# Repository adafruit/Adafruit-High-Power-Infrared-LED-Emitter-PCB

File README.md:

## Adafruit High Power Infrared LED Emitter PCB

<a href="http://www.adafruit.com/products/5639"><br/>
Click here to purchase one from the Adafruit shop</a>

PCB files for the Adafruit High Power Infrared LED Emitter. 

Format is EagleCAD schematic and board layout
* https://www.adafruit.com/product/5639

### Description

*pew* *pew*! This board is like a little ray gun for infrared light, with two high powered LED outputs. When controlled with the onboard N-Channel FET driver, you'll be blasting 100mA-200mA of current pulsing through each LED for 10+ meters of range! This is the easiest way to get great IR emitter range without wiring up a bunch of parts.

By using a 2mm pitch STEMMA JST PH cable with headers or alligator clips on the end, you can easily wire this board up without any soldering at all.

This board features a power transistor so you just need to provide about 3-5V DC power to the V+ power in, ground for ground, and then a 3-5V logic level signal on the input pin. When the pin is high, the LEDs are on, when the signal pin is low, the LEDs are off. Since humans don't see in IR, there's a red LED that will let you know when the IR LEDs are lit. Two LEDs are pre-soldered to the PCB, one pointing up and one pointing out. If you want even MORE coverage, there's a spot to solder in a separate 5mm IR LED (not included).

If powering with 5V, the board will draw about 200mA per LED (400mA total) when pulsing on. If powering with 3V the board will draw about 100mA per LED (200mA total). We don't recommend keeping the LEDs on for long periods at this current draw, they're for remote control transmission more than IR illumination.

Each STEMMA board comes with a fully assembled and tested PCB but no cable. No soldering is required to use it, but you will need to pick up  a 2mm pitch, 3-pin STEMMA JST PH cable. Alternatively, if you do want to solder, there's a 0.1" spaced header for power/ground/signal.

### License

Adafruit invests time and resources providing this open source design, please support Adafruit and open-source hardware by purchasing products from [Adafruit](https://www.adafruit.com)!

Designed by Limor Fried/Ladyada for Adafruit Industries.

Creative Commons Attribution/Share-Alike, all text above must be included in any redistribution. 
See license.txt for additional details.

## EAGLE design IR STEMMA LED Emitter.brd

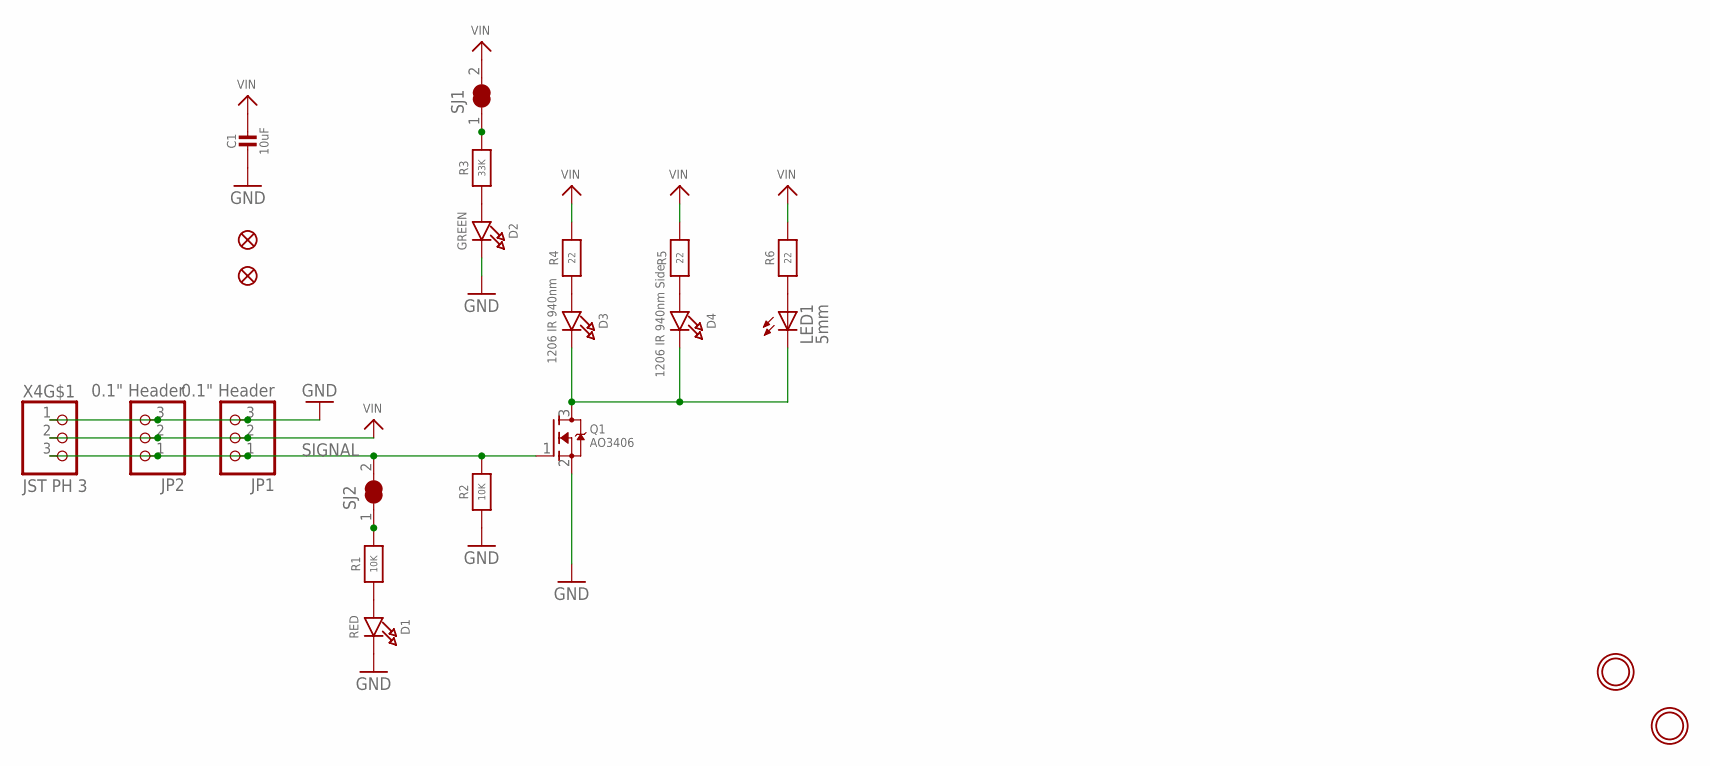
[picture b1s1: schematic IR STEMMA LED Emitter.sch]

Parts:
C1: 10uF; 0805-NO
D1: RED; CHIPLED_0603_NOOUTLINE
D2: GREEN; CHIPLED_0603_NOOUTLINE
D3: 1206 IR 940nm; CHIPLED_1206
D4: 1206 IR 940nm Side; LED_1206_SIDE
FID2, FID3: FIDUCIAL_1MM
JP1: 0.1" Header; 1X03_OVAL
JP2: 0.1" Header; 1X03_ROUND
LED1: 5mm; LED5MM
Q1: AO3406; SOT23-WIDE
R1, R2: 10K; 0603-NO
R3: 33K; 0603-NO
R4, R5, R6: 22; 0603-NO
SJ1, SJ2: SOLDERJUMPER_CLOSED; SOLDERJUMPER_CLOSEDWIRE
U$1, U$8: MOUNTINGHOLE2.5; MOUNTINGHOLE_2.5_PLATED
X4: JST PH 3; JSTPH3

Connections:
GND: C1.2, D1.C, D2.C, JP1.3, JP2.3, Q1.2 (S), R2.1, X4.1
unnamed: R3.2, SJ1.1
unnamed: D1.A, R1.1
unnamed: R1.2, SJ2.1
unnamed: D3.C, D4.C, LED1.K (C), Q1.3 (D)
unnamed: D3.A, R4.1
unnamed: D4.A, R5.1
unnamed: LED1.A, R6.1
unnamed: D2.A, R3.1
SIGNAL: JP1.1, JP2.1, Q1.1 (G), R2.2, SJ2.2, X4.3
VIN: C1.1, JP1.2, JP2.2, R4.2, R5.2, R6.2, SJ1.2, X4.2

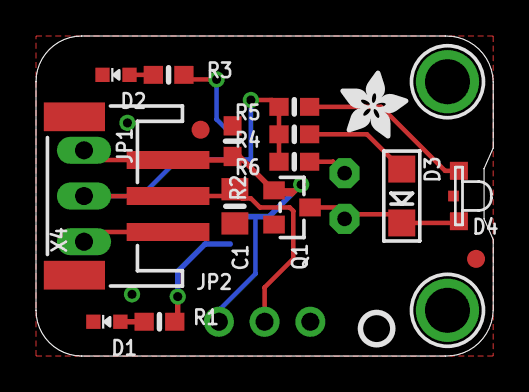
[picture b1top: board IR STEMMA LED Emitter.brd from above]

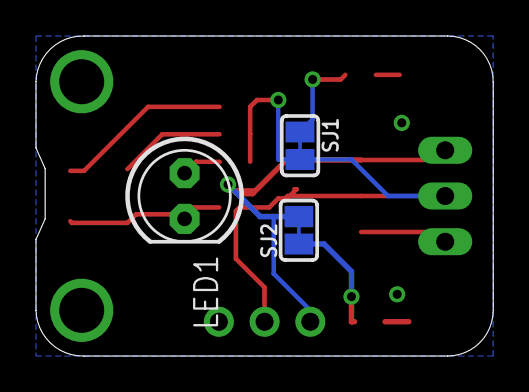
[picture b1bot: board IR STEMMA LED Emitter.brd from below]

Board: 2 copper layers, 25.4 x 17.8 mm, 39 parts (14 on the bottom side), 11 nets.

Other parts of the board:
PLABEL0: PLABEL0
PLABEL00: PLABEL00
PLABEL1: PLABEL1
PLABEL2: PLABEL2
PLABEL3: PLABEL3
PLABEL4: PLABEL4
PLABEL5: PLABEL5
PLABEL6: PLABEL6
PLABEL7: PLABEL7
PLABEL8: PLABEL8
PLABEL9: PLABEL9
PLABEL10: PLABEL10
PLABEL11: PLABEL11
PLABEL13: PLABEL13
PLABEL14: PLABEL14
U$5: PCBFEAT-REV-040
U$10: ADAFRUIT_3.5MM

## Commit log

2022-11-08 adding cookiecutter output

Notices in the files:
parts and their libraries:
microbuilder: This work is placed in the public domain, and may be freely used for commercial and non-commercial work with the following conditions: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
